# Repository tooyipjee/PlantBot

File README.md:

# Plant Bot: Automate Plant Care 🌱

## High-Level Summary

Plant Bot is a cutting-edge device designed to revolutionize plant care. Powered by USB, it seamlessly integrates into your pot, transforming it into an active participant in plant care. With features like a moisture sensor, integrated pump driver, and multi-color LED control, it's the ultimate companion for every plant enthusiast.

Available on 

---

## Detailed Description

### What is it?

Plant Bot is not just a device; it's a solution to modern plant care challenges. Designed for both casual plant owners and enthusiasts, it offers:

- **Corrosion-Resistant Capacitive Moisture Sensor:** Say goodbye to guesswork. Know exactly when your plant needs water.
- **Integrated Pump Driver & LED Control:** Automated care with visual feedback. The LED's color spectrum ranges from red (indicating dry soil) to blue (indicating moist soil).
- **Connectivity:** With both WiFi and Bluetooth capabilities, stay connected with your plants from anywhere.
- **Battery-Powered Operation:** Designed as a low-power IoT device, ensuring longevity and reliability.

Leveraging open-source projects, Plant Bot supports programming via Micropython and Arduino. For advanced users, the ESP-IDF tool offers maximum customization.

---

## Use Cases

### Fully Automated Plant Care

The sample code provided showcases Plant Bot's capabilities in measuring soil moisture and light levels, taking actions based on the data. The intuitive LED color spectrum offers a visual representation of soil conditions, while an additional LED signals pump activation for hydration. Built on the ESP32 platform, it boasts comprehensive connectivity, transmitting data to platforms like Thingspeak.

### Connected Plant Node

Harness the power of Plant Bot's low-power design to connect your plants to the internet wirelessly. Demos are available that allow Plant Bot to send Telegram notifications or relay measurements to IoT platforms. With efficient power consumption, a single coin cell battery can last up to a week with daily updates.

---

## How to Run the Demo Script

1. **Setup:** Ensure you have the Arduino IDE installed on your computer.
2. **Connect:** Plug in your ESP32-C3 device to your computer via USB.
3. **Integrated JTAG:** Ensure the JTAG is setup. In Tools, "USB CDC On Boot" is Enabled and JTAG Adapter is USB JTAG Adapter.
5. **Load Script:** Open one of the demo script provided in the Arduino IDE.
6. **Select Board:** From the 'Tools' menu, select 'Board' and choose 'ESP32-C3'.
7. **Select Port:** Select the port for the Plant-Bot device, if nothing pops up, unplug the device, hold the settings button and plug it back into the computer while still holding the button. It should appear now.
8. **Upload:** Click on the 'Upload' button to program the ESP32-C3.
9. **Monitor:** Open the Serial Monitor to view outputs and ensure the script runs successfully.

For any issues or further instructions, please refer to the documentation or raise an issue in the repo.

---

**Acknowledgments:** A special thank you to JLCPCB for their unwavering support throughout this project. Their expertise in rapid prototyping without compromising on quality has been invaluable.

## License

MIT License

Copyright (c) 2023 elektroThing

Permission is hereby granted, free of charge, to any person obtaining a copy
of this software and associated documentation files (the "Software"), to deal
in the Software without restriction, including without limitation the rights
to use, copy, modify, merge, publish, distribute, sublicense, and/or sell
copies of the Software, and to permit persons to whom the Software is
furnished to do so, subject to the following conditions:

The above copyright notice and this permission notice shall be included in all
copies or substantial portions of the Software.

THE SOFTWARE IS PROVIDED "AS IS", WITHOUT WARRANTY OF ANY KIND, EXPRESS OR
IMPLIED, INCLUDING BUT NOT LIMITED TO THE WARRANTIES OF MERCHANTABILITY,
FITNESS FOR A PARTICULAR PURPOSE AND NONINFRINGEMENT. IN NO EVENT SHALL THE
AUTHORS OR COPYRIGHT HOLDERS BE LIABLE FOR ANY CLAIM, DAMAGES OR OTHER
LIABILITY, WHETHER IN AN ACTION OF CONTRACT, TORT OR OTHERWISE, ARISING FROM,
OUT OF OR IN CONNECTION WITH THE SOFTWARE OR THE USE OR OTHER DEALINGS IN THE
SOFTWARE.

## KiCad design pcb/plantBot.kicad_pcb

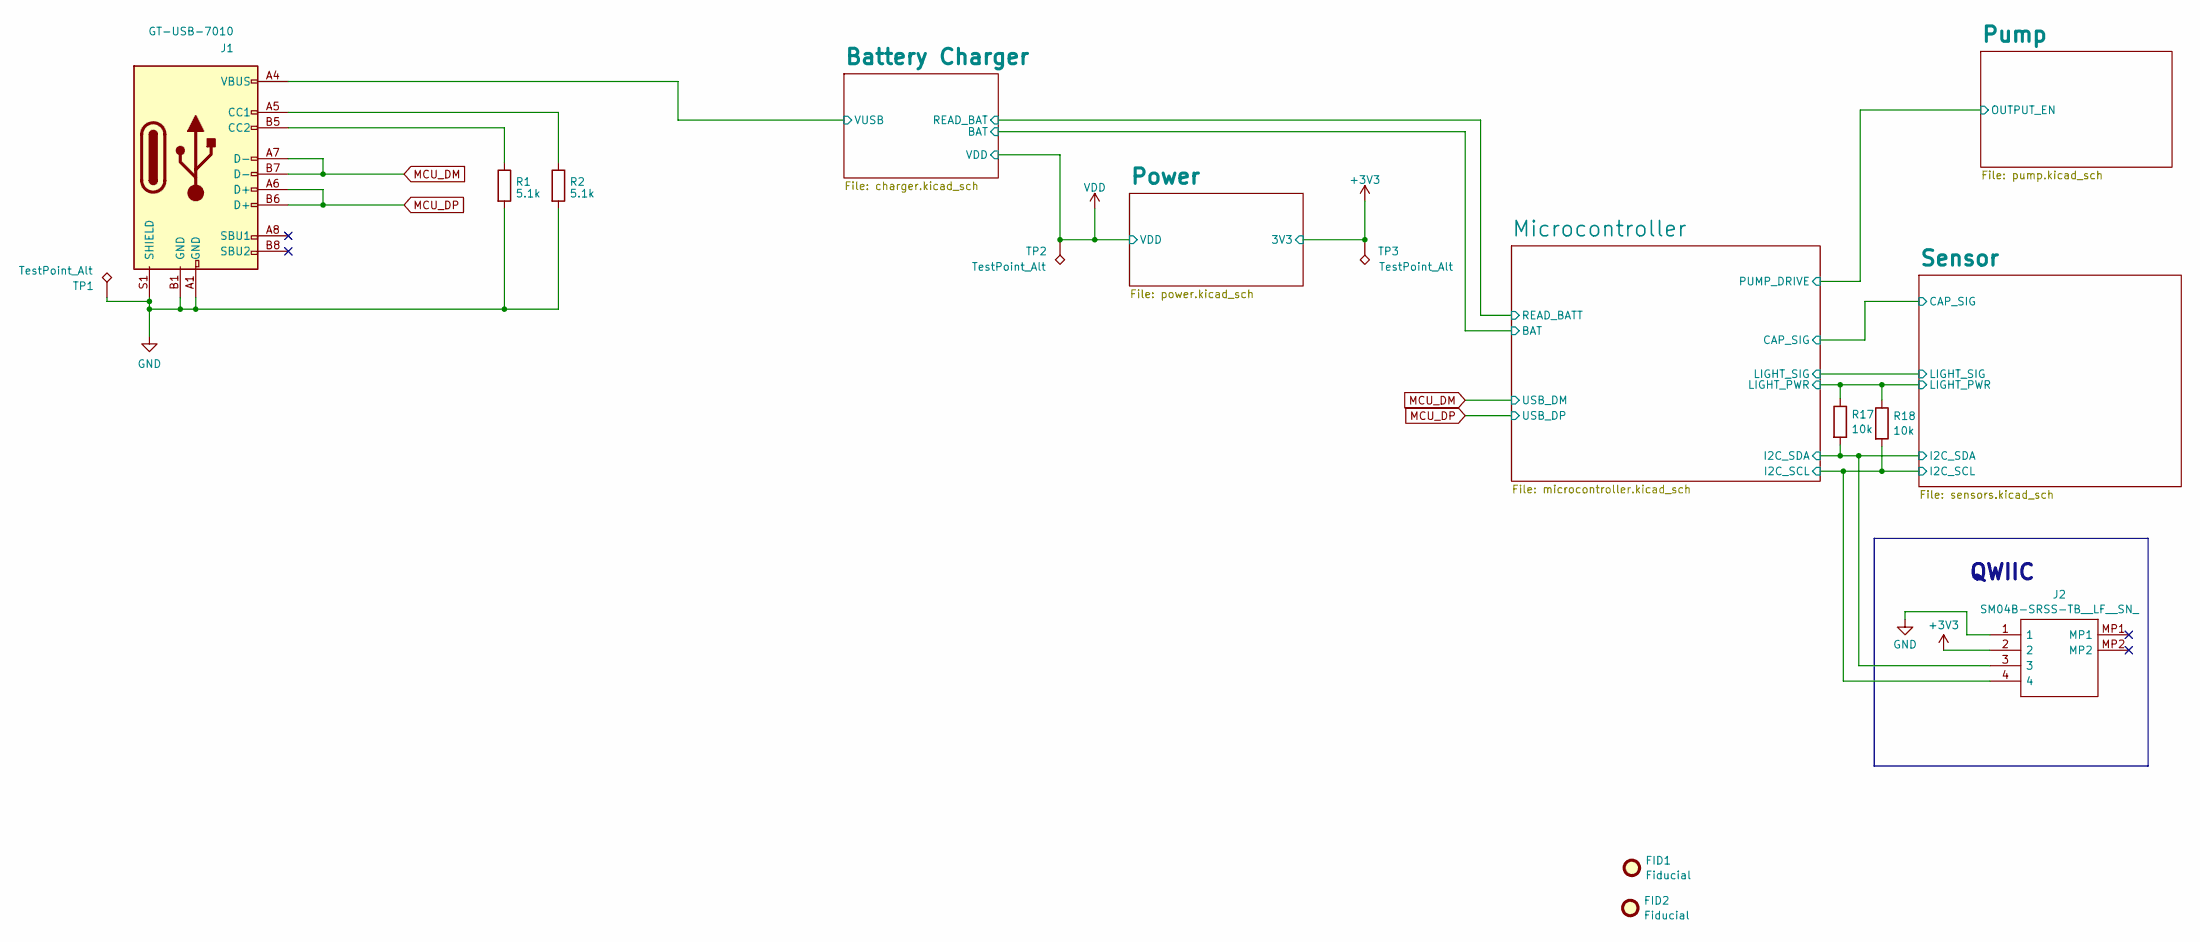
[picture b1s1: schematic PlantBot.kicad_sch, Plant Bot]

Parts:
FID1: Fiducial; Product Stamp
FID2: Fiducial; jlcpcb_logo_2mm
J1: GT-USB-7010; GT-USB-7010A; LCSC C963370
J2: SM04B-SRSS-TB__LF__SN_; SM04BSRSSTBLFSN; Manufacturer_Part_Number SM04B-SRSS-TB (LF)(SN); LCSC C160404
R1, R2: 5.1k; R_0402_1005Metric; LCSC C2906948
R17, R18: 10k; R_0402_1005Metric; LCSC C25744
TP1, TP2, TP3: TestPoint_Alt; TestPoint_Pad_1.0x1.0mm

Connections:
+3V3: J2.2, TP3.1; also elsewhere on the board
/Battery Charger/VUSB: J1.A4 (VBUS), J1.A9 (VBUS), J1.B4 (VBUS), J1.B9 (VBUS); also elsewhere on the board
/Microcontroller/I2C_SCL: J2.4, R18.2; also elsewhere on the board
/Microcontroller/I2C_SDA: J2.3, R17.2; also elsewhere on the board
GND: J1.A1 (GND), J1.B1 (GND), J1.S1 (SHIELD), J2.1, R1.2, R2.2, TP1.1; also elsewhere on the board
I2C_PWR: R17.1, R18.1; also elsewhere on the board
MCU_DM: J1.A7 (D-), J1.B7 (D-); also elsewhere on the board
MCU_DP: J1.A6 (D+), J1.B6 (D+); also elsewhere on the board
unnamed: J1.A5 (CC1), R2.1
unnamed: J1.B5 (CC2), R1.1
VDD: TP2.1; also elsewhere on the board

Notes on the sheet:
QWIIC

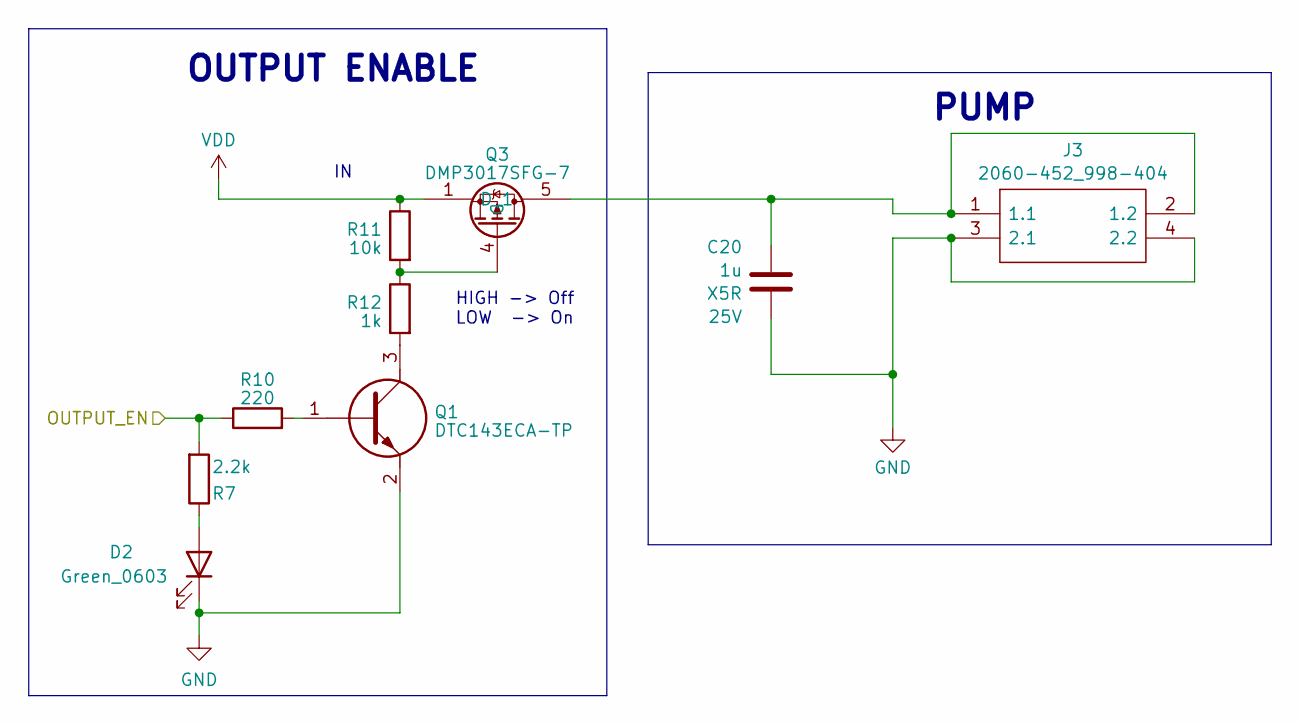
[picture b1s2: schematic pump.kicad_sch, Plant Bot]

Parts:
C20: 1u; C_0402_1005Metric; Voltage 25V; LCSC C52923
D2: Green_0603; LED_0603_1608Metric; LCSC C72043
J3: 2060-452_998-404; 2060452998404; Manufacturer_Part_Number 2060-452/998-404; LCSC C2765055
Q1: DTC143ECA-TP; SOT95P237X125-3N; Manufacturer_Part_Number DTC143ECA-TP; Mouser Part Number 833-DTC143ECA-TP
Q3: DMP3017SFG-7; DMP3007SFG7; Manufacturer_Part_Number DMP3017SFG-7; Mouser Part Number 621-DMP3017SFG-7
R7: 2.2k; R_0402_1005Metric; LCSC C25879
R10: 220; R_0402_1005Metric; LCSC C25091
R11: 10k; R_0402_1005Metric; LCSC C25744
R12: 1k; R_0402_1005Metric; LCSC C11702

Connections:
/Microcontroller/PUMP_DRIVE: R7.2, R10.1; also elsewhere on the board
GND: C20.2, D2.1 (K), J3.3 (2.1), J3.4 (2.2), Q1.2; also elsewhere on the board
unnamed: D2.2 (A), R7.1
unnamed: C20.1, J3.1 (1.1), J3.2 (1.2), Q3.5 (D_1), Q3.6, Q3.7, Q3.8, Q3.9
unnamed: Q1.1, R10.2
unnamed: Q1.3, R12.2
unnamed: Q3.4 (G), R11.2, R12.1
VDD: Q3.1, Q3.2, Q3.3, R11.1; also elsewhere on the board

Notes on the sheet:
OUTPUT ENABLE
PUMP
HIGH -> Off LOW -> On

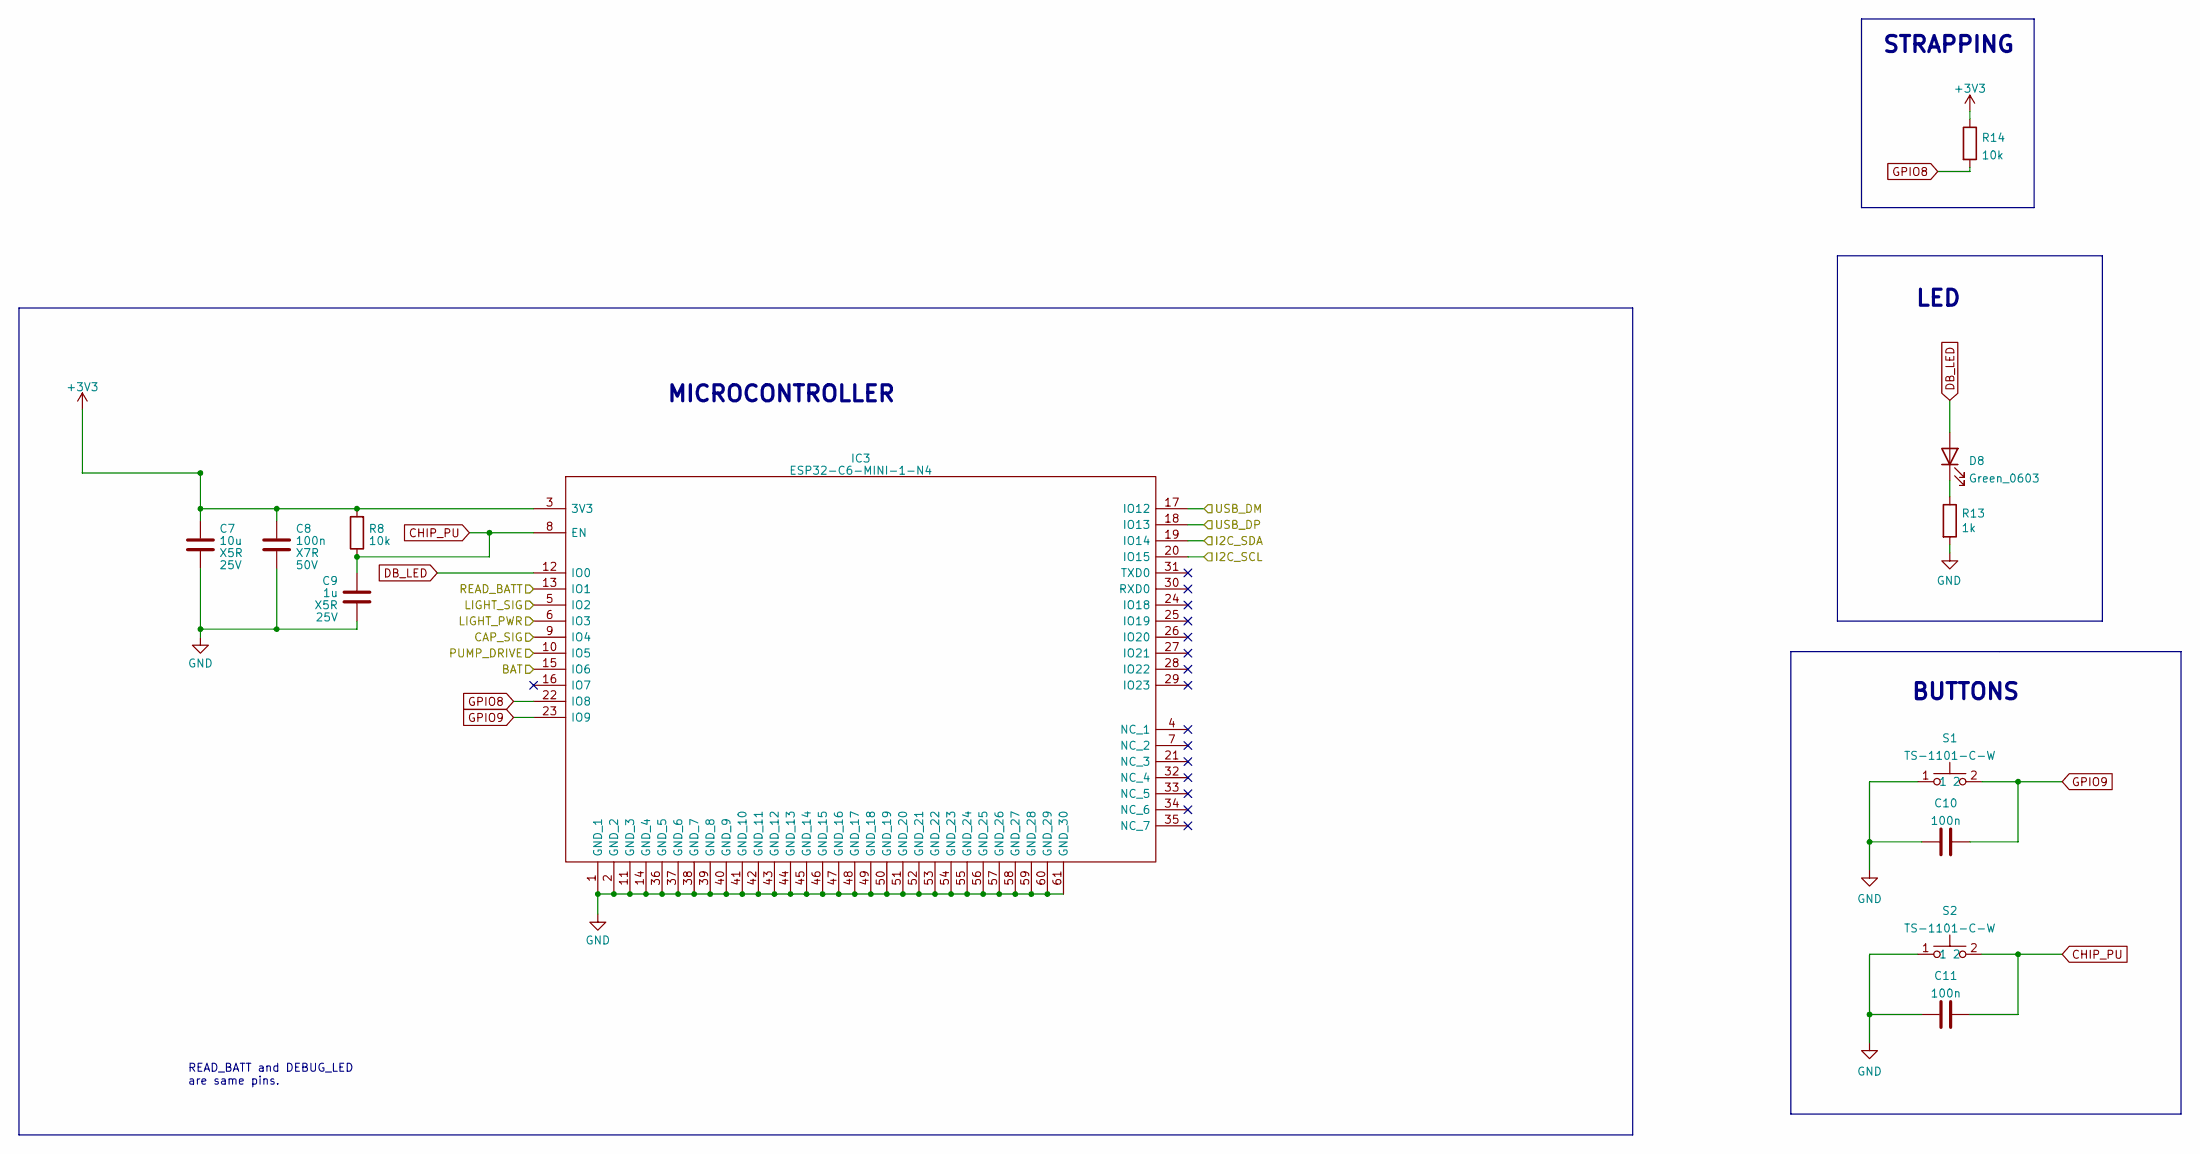
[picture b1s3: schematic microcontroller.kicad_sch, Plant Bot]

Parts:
C7: 10u; C_0805_2012Metric; Voltage 25V; LCSC C15850
C8: 100n; C_0402_1005Metric; Voltage 50V; LCSC C307331
C9: 1u; C_0402_1005Metric; Voltage 25V; LCSC C52923
C10, C11: 100n; C_0402_1005Metric; LCSC C307331
D8: Green_0603; LED_0603_1608Metric; LCSC C72043
IC3: ESP32-C6-MINI-1-N4; ESP32C6MINI1N4; Manufacturer_Part_Number ESP32-C6-MINI-1-N4; Mouser Part Number 356-ESP32C6MINI-1-N4
R8, R14: 10k; R_0402_1005Metric; LCSC C25744
R13: 1k; R_0402_1005Metric; LCSC C11702
S1, S2: TS-1101-C-W; TS1101CW; Manufacturer_Part_Number TS-1101-C-W; LCSC C318938

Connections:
+3V3: C7.1, C8.1, IC3.3 (3V3), R8.2, R14.1; also elsewhere on the board
/Battery Charger/BAT: IC3.15 (IO6); also elsewhere on the board
/Battery Charger/READ_BAT: IC3.13 (IO1); also elsewhere on the board
/Microcontroller/CAP_SIG: IC3.9 (IO4); also elsewhere on the board
/Microcontroller/I2C_SCL: IC3.20 (IO15); also elsewhere on the board
/Microcontroller/I2C_SDA: IC3.19 (IO14); also elsewhere on the board
/Microcontroller/LIGHT_SIG: IC3.5 (IO2); also elsewhere on the board
/Microcontroller/PUMP_DRIVE: IC3.10 (IO5); also elsewhere on the board
CHIP_PU: C9.2, C11.2, IC3.8 (EN), R8.1, S2.2
DB_LED: D8.2 (A), IC3.12 (IO0)
GND: C7.2, C8.2, C9.1, C10.1, C11.1, IC3.1 (GND_1), IC3.2 (GND_2), IC3.11 (GND_3), IC3.14 (GND_4), IC3.36 (GND_5), IC3.37 (GND_6), IC3.38 (GND_7), IC3.39 (GND_8), IC3.40 (GND_9), IC3.41 (GND_10), IC3.42 (GND_11), IC3.43 (GND_12), IC3.44 (GND_13), IC3.45 (GND_14), IC3.46 (GND_15), IC3.47 (GND_16), IC3.48 (GND_17), IC3.49 (GND_18), IC3.50 (GND_19), IC3.51 (GND_20), IC3.52 (GND_21), IC3.53 (GND_22), IC3.54 (GND_23), IC3.55 (GND_24), IC3.56 (GND_25), IC3.57 (GND_26), IC3.58 (GND_27), IC3.59 (GND_28), IC3.60 (GND_29), IC3.61 (GND_30), R13.2, S1.1, S2.1; also elsewhere on the board
GPIO8: IC3.22 (IO8), R14.2
GPIO9: C10.2, IC3.23 (IO9), S1.2
I2C_PWR: IC3.6 (IO3); also elsewhere on the board
MCU_DM: IC3.17 (IO12); also elsewhere on the board
MCU_DP: IC3.18 (IO13); also elsewhere on the board
unnamed: D8.1 (K), R13.1

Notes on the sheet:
STRAPPING
READ_BATT and DEBUG_LED are same pins.
LED
MICROCONTROLLER
BUTTONS

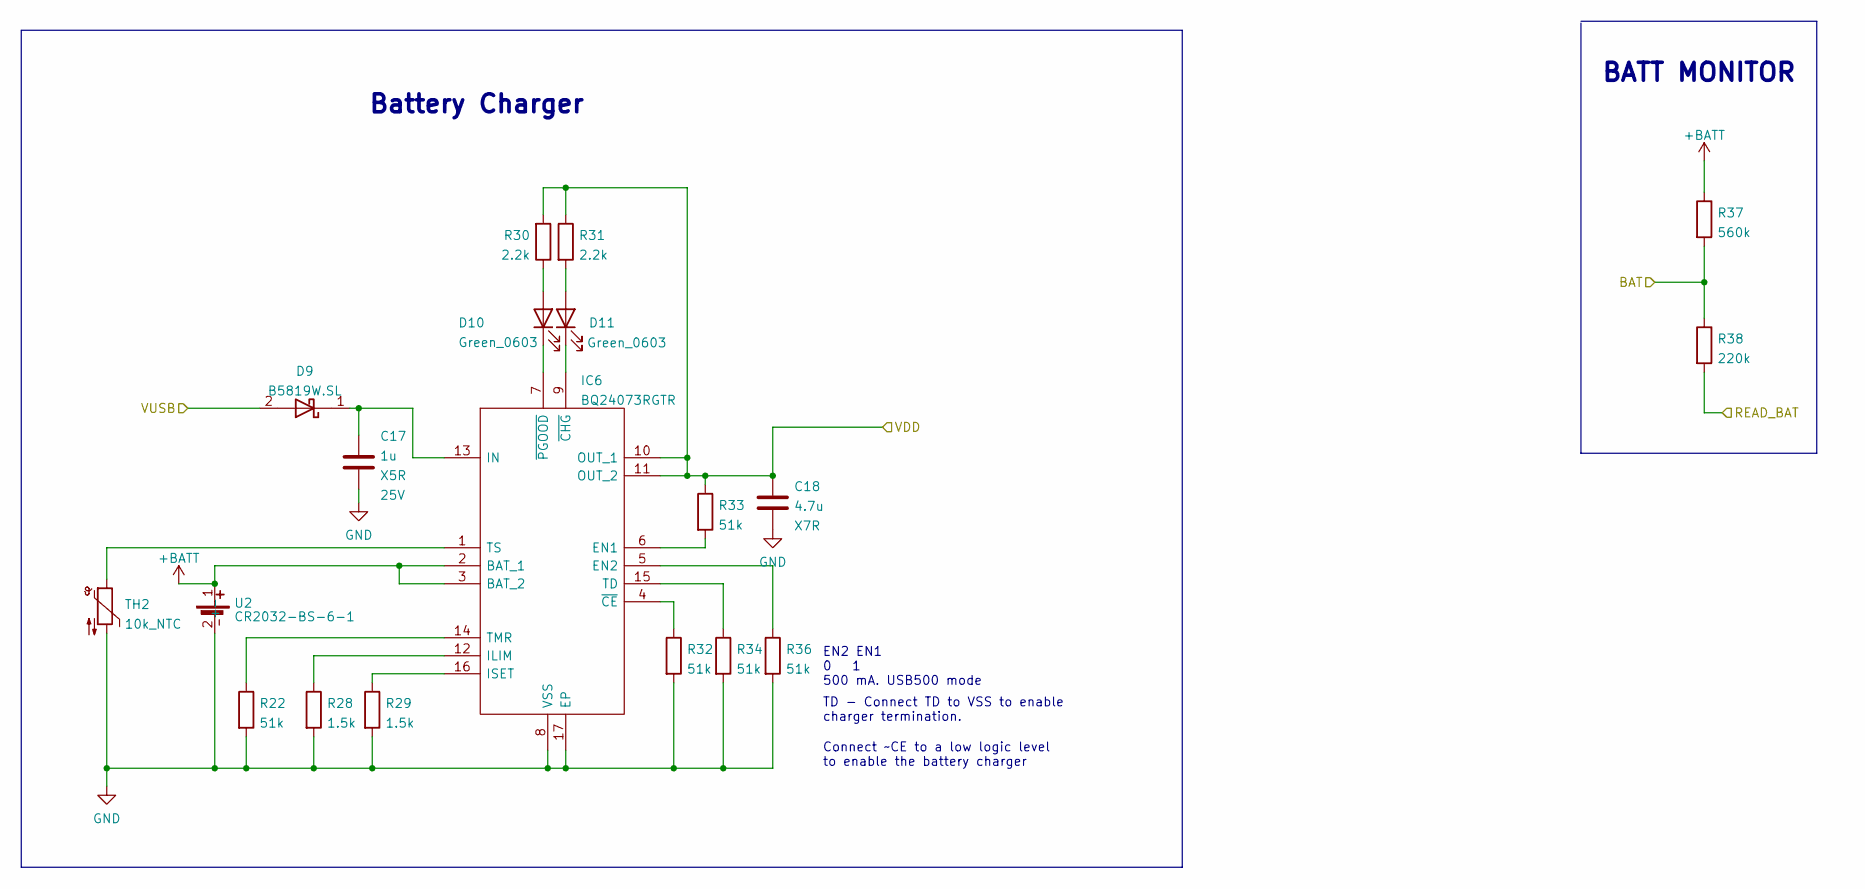
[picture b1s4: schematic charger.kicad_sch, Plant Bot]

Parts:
C17: 1u; C_0402_1005Metric; Voltage 25V; LCSC C52923
C18: 4.7u; C_1206_3216Metric; Rating 50V; LCSC C29823
D9: B5819W.SL; B5819WSL; Manufacturer_Part_Number B5819W.SL; LCSC C8598
D10, D11: Green_0603; LED_0603_1608Metric; LCSC C72043
IC6: BQ24073RGTR; QFN50P300X300X100-17N-D; Manufacturer_Part_Number BQ24073RGTR; Mouser Part Number 595-BQ24073RGTR
R22, R32, R33, R34, R36: 51k; R_0402_1005Metric; LCSC C25794
R28, R29: 1.5k; R_0402_1005Metric; LCSC C25867
R30, R31: 2.2k; R_0402_1005Metric; LCSC C25879
R37: 560k; R_0603_1608Metric; LCSC C23203
R38: 220k; R_0402_1005Metric; LCSC C25767
TH2: 10k_NTC; R_0402_1005Metric; MPN NCU15XH103F6SRC; LCSC C333993
U2: CR2032-BS-6-1; CR2032BS61; Manufacturer_Part_Number CR2032-BS-6-1; LCSC C70377

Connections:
+BATT: IC6.2 (BAT_1), IC6.3 (BAT_2), R37.1, U2.1 (+)
/Battery Charger/BAT: R37.2, R38.1; also elsewhere on the board
/Battery Charger/READ_BAT: R38.2; also elsewhere on the board
/Battery Charger/VUSB: D9.2; also elsewhere on the board
GND: C17.2, C18.2, IC6.8 (VSS), IC6.17 (EP), R22.2, R28.2, R29.2, R32.2, R34.2, R36.2, TH2.2, U2.2 (-); also elsewhere on the board
unnamed: D10.2 (A), R30.1
unnamed: D10.1 (K), IC6.7 (~PGOOD)
unnamed: D11.2 (A), R31.2
unnamed: D11.1 (K), IC6.9 (~CHG)
unnamed: IC6.6 (EN1), R33.2
unnamed: IC6.5 (EN2), R36.1
unnamed: IC6.12 (ILIM), R28.1
unnamed: C17.1, D9.1, IC6.13 (IN)
unnamed: IC6.16 (ISET), R29.1
unnamed: IC6.15 (TD), R34.1
unnamed: IC6.14 (TMR), R22.1
unnamed: IC6.1 (TS), TH2.1
unnamed: IC6.4 (~CE), R32.1
VDD: C18.1, IC6.10 (OUT_1), IC6.11 (OUT_2), R30.2, R31.1, R33.1; also elsewhere on the board

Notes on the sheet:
Connect ~CE to a low logic level to enable the battery charger
TD - Connect TD to VSS to enable charger termination.
Battery Charger
BATT MONITOR
EN2 EN1 0 1 500 mA. USB500 mode

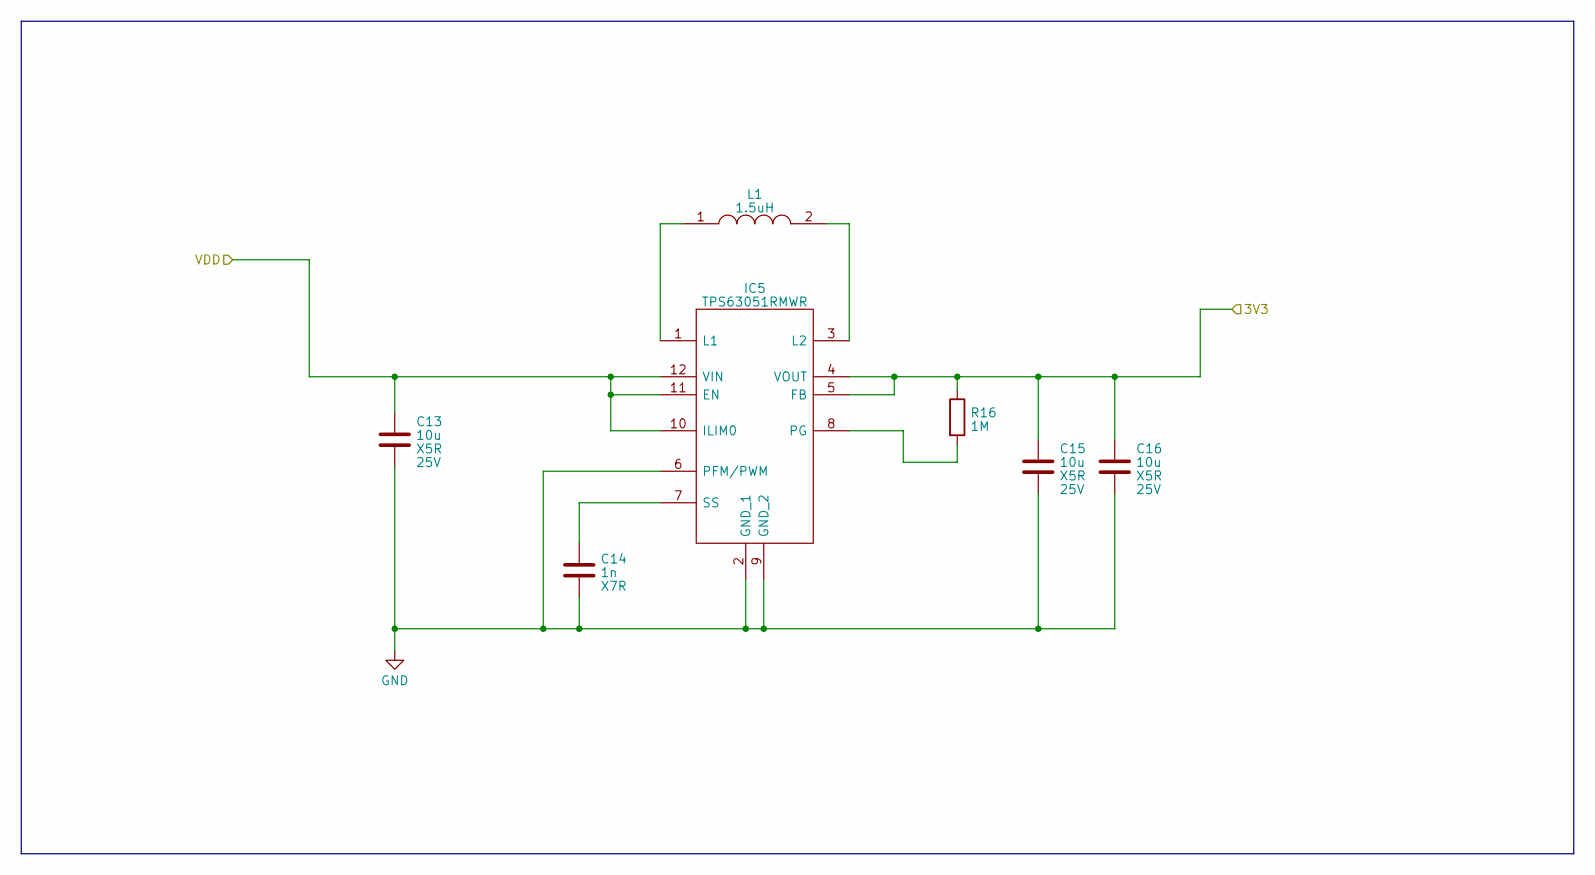
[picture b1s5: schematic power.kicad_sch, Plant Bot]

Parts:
C13, C15, C16: 10u; C_0805_2012Metric; Voltage 25V; LCSC C15850
C14: 1n; C_0402_1005Metric; LCSC C1523
IC5: TPS63051RMWR; QFN50P250X250X100-12N-D; Manufacturer_Part_Number TPS63051RMWR; Mouser Part Number 595-TPS63051RMWR
L1: 1.5uH; L_0805_2012Metric; LCSC C2042639
R16: 1M; R_0402_1005Metric; LCSC C26083

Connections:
+3V3: C15.1, C16.1, IC5.4 (VOUT), IC5.5 (FB), R16.1; also elsewhere on the board
GND: C13.2, C14.2, C15.2, C16.2, IC5.2 (GND_1), IC5.6 (PFM/PWM), IC5.9 (GND_2); also elsewhere on the board
unnamed: IC5.1 (L1), L1.1
unnamed: IC5.3 (L2), L1.2
unnamed: IC5.8 (PG), R16.2
unnamed: C14.1, IC5.7 (SS)
VDD: C13.1, IC5.10 (ILIM0), IC5.11 (EN), IC5.12 (VIN); also elsewhere on the board

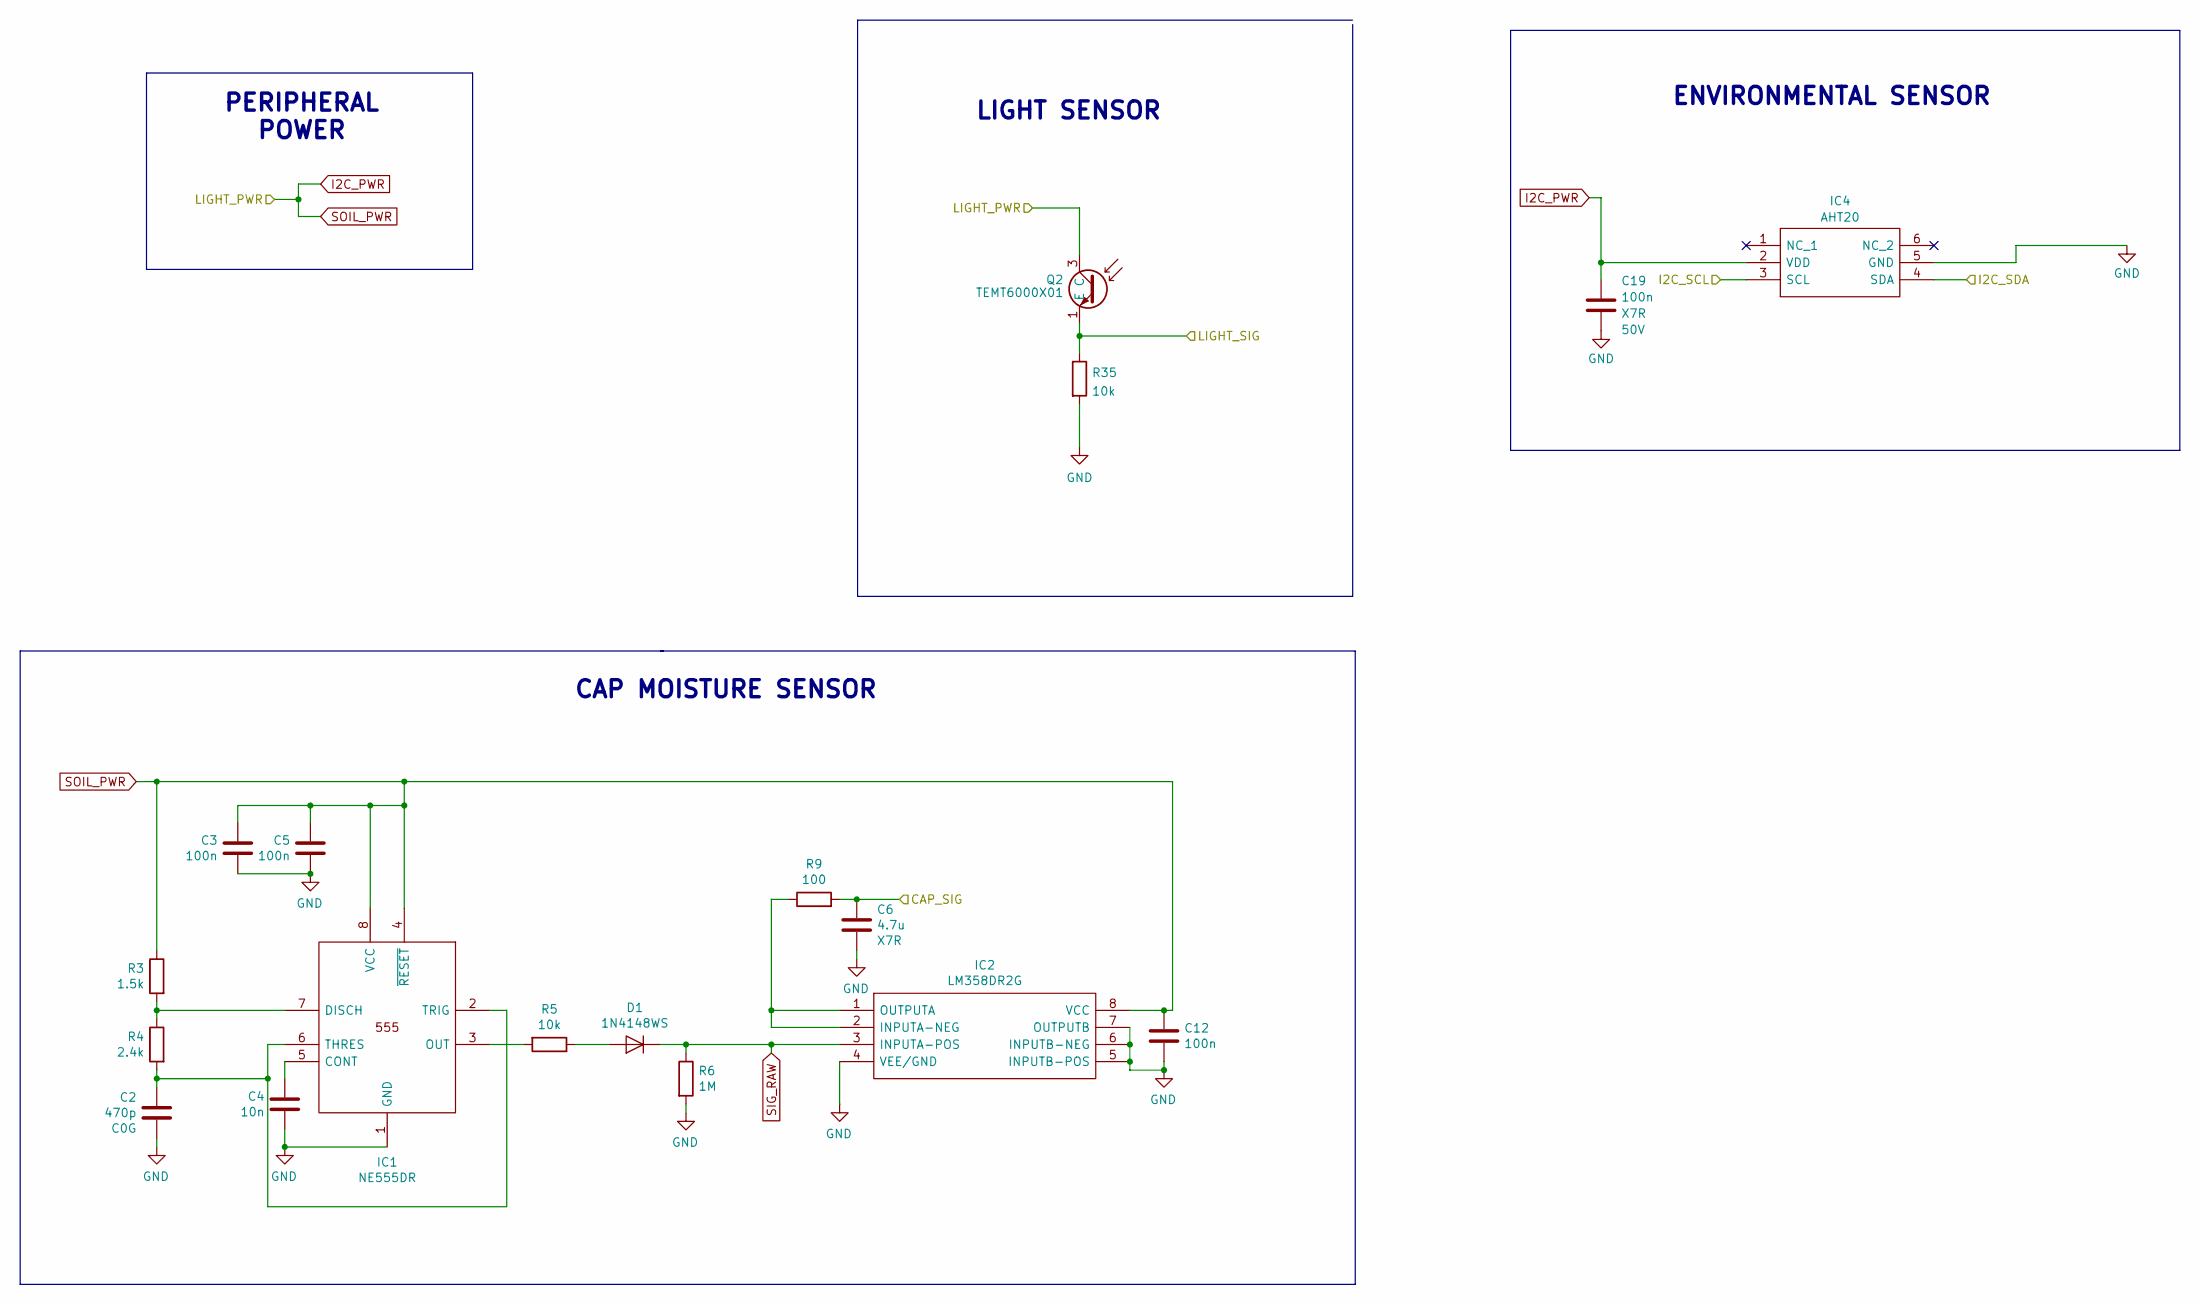
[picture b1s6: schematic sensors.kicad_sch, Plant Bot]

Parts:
C2: 470p; C_0603_1608Metric; Rating 25V; LCSC C1620
C3, C5, C12: 100n; C_0402_1005Metric; LCSC C307331
C4: 10n; C_0402_1005Metric; LCSC C15195
C6: 4.7u; C_1206_3216Metric; Rating 50V; LCSC C29823
C19: 100n; C_0402_1005Metric; Voltage 50V; LCSC C307331
D1: 1N4148WS; D_SOD-323F; LCSC C2128
IC1: NE555DR; SOIC127P600X175-8N; Manufacturer_Part_Number NE555DR; Mouser Part Number 595-NE555DR
IC2: LM358DR2G; SOIC127P600X175-8N; Mouser Part Number 863-LM358DR2G
IC4: AHT20; Manufacturer_Part_Number AHT20; LCSC C2757850
Q2: TEMT6000X01; Manufacturer_Part_Number TEMT6000X01; Mouser Part Number 78-TEMT6000
R3: 1.5k; R_0402_1005Metric; LCSC C25867
R4: 2.4k; R_0402_1005Metric; LCSC C25882
R5, R35: 10k; R_0402_1005Metric; LCSC C25744
R6: 1M; R_0402_1005Metric; LCSC C26083
R9: 100; R_0402_1005Metric; LCSC C25076

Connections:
/Microcontroller/CAP_SIG: C6.1, R9.2; also elsewhere on the board
/Microcontroller/I2C_SCL: IC4.3 (SCL); also elsewhere on the board
/Microcontroller/I2C_SDA: IC4.4 (SDA); also elsewhere on the board
/Microcontroller/LIGHT_SIG: Q2.1 (E), Q2.2 (E), R35.1; also elsewhere on the board
GND: C2.2, C3.2, C4.2, C5.2, C6.2, C12.2, C19.2, IC1.1 (GND), IC2.4 (VEE/GND), IC2.5 (INPUTB-POS), IC2.6 (INPUTB-NEG), IC2.7 (OUTPUTB), IC4.5 (GND), R6.2, R35.2; also elsewhere on the board
I2C_PWR: C3.1, C5.1, C12.1, C19.1, IC1.4 (~RESET), IC1.8 (VCC), IC2.8 (VCC), IC4.2 (VDD), Q2.3 (C), R3.1; also elsewhere on the board
unnamed: D1.2 (A), R5.1
unnamed: C4.1, IC1.5 (CONT)
unnamed: IC1.7 (DISCH), R3.2, R4.1
unnamed: IC1.3 (OUT), R5.2
unnamed: C2.1, IC1.2 (TRIG), IC1.6 (THRES), R4.2
unnamed: IC2.1 (OUTPUTA), IC2.2 (INPUTA-NEG), R9.1
SIG_RAW: D1.1 (K), IC2.3 (INPUTA-POS), R6.1

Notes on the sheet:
ENVIRONMENTAL SENSOR
CAP MOISTURE SENSOR
PERIPHERAL POWER
LIGHT SENSOR

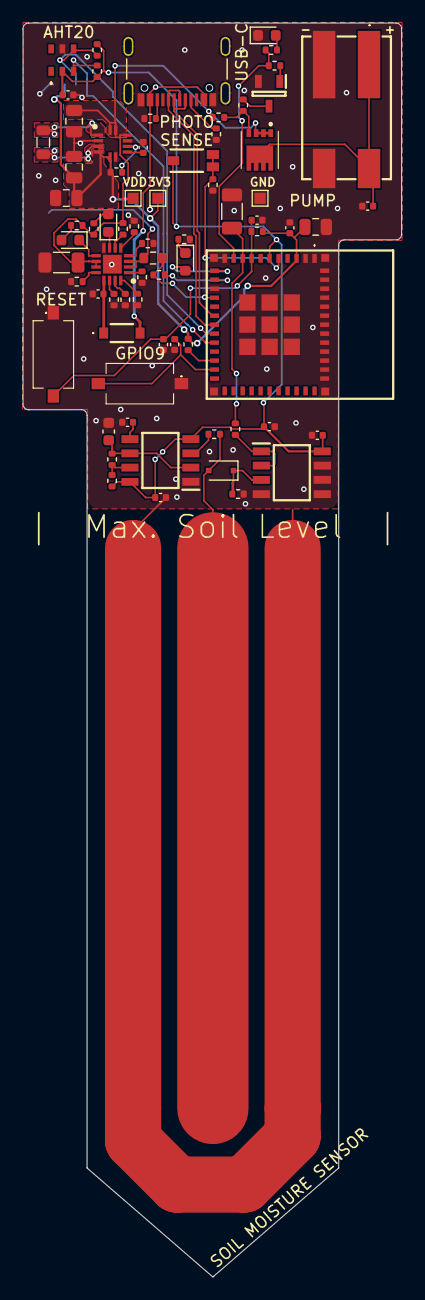
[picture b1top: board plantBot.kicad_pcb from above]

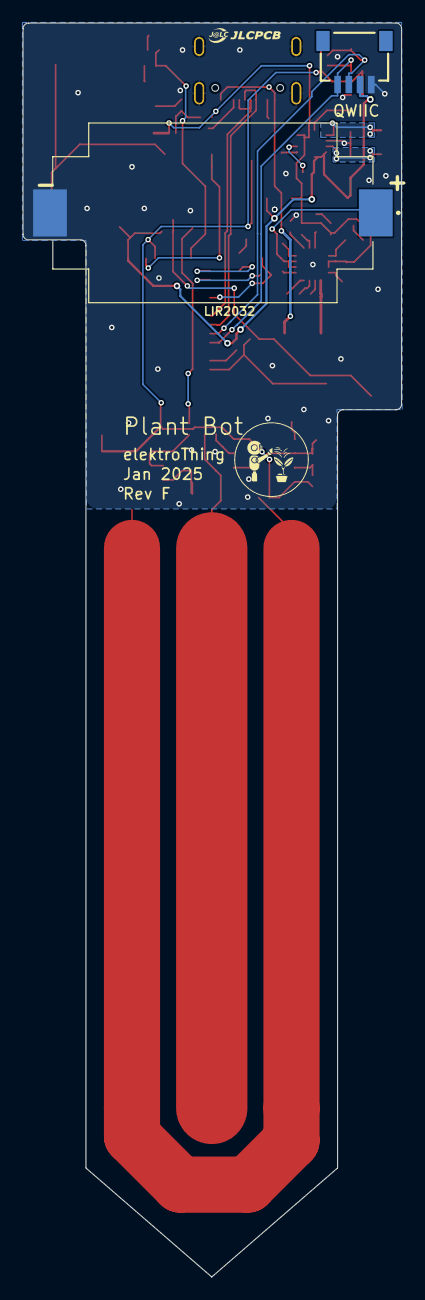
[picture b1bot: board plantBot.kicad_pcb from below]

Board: 2 copper layers, 33.7 x 111.6 mm, 77 parts (5 on the bottom side), 51 nets.

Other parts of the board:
F*: LOGO; logo_10mm

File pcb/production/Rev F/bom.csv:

Designator,Footprint,Quantity,Value,LCSC Part #
"C10, C11, C12, C19, C3, C5, C8",0402,7,100n,C307331
"C13, C15, C16, C7",0805,4,10u,C15850
C14,0402,1,1n,C1523
"C17, C20, C9",0402,3,1u,C52923
"C18, C6",1206,2,4.7u,C29823
C2,0603,1,470p,C1620 
C4,0402,1,10n,C15195
D1,D_SOD-323F,1,1N4148WS,C2128
"D10, D11, D2, D8",0603,4,Green_0603,C72043
D9,B5819WSL,1,B5819W.SL,C8598
IC1,SOIC127P600X175-8N,1,NE555DR,C7593
IC2,SOIC127P600X175-8N,1,LM358DR2G,C7950
IC3,ESP32C6MINI1N4,1,ESP32-C6-MINI-1-N4,C5736265
IC4,AHT20,1,AHT20,C2757850
IC5,QFN50P250X250X100-12N-D,1,TPS63051RMWR,C139412
IC6,QFN50P300X300X100-17N-D,1,BQ24073RGTR,C15220
J1,GT-USB-7010A,1,GT-USB-7010,C963370
J2,SM04BSRSSTBLFSN,1,SM04B-SRSS-TB__LF__SN_,C160404
J3,2060452998404,1,2060-452_998-404,C2765055
L1,0805,1,1.5uH,C2042639
Q1,SOT95P237X125-3N,1,DTC143ECA-TP,
Q2,TEMT6000X01,1,TEMT6000X01,C94098
Q3,DMP3007SFG7,1,DMP3017SFG-7,DMP3017SFG
"R1, R2",0402,2,5.1k,C2906948
R10,0402,1,220,C25091
"R11, R14, R17, R18, R35, R5, R8",0402,7,10k,C25744
"R12, R13",0402,2,1k,C11702
"R16, R6",0402,2,1M,C26083
"R22, R32, R33, R34, R36",0402,5,51k,C25794
"R28, R29, R3",0402,3,1.5k,C25867
"R30, R31, R7",0402,3,2.2k,C25879
R37,0603,1,560k,C23203
R38,0402,1,220k,C25767
R4,0402,1,2.4k,C25882
R9,0402,1,100,C25076
"S1, S2",TS1101CW,2,TS-1101-C-W,C318938
TH2,0402,1,10k_NTC,C333993
"TP1, TP2, TP3",TestPoint_Pad_1.0x1.0mm,3,TestPoint_Alt,
U2,CR2032BS61,1,CR2032-BS-6-1,C70377

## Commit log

2023-06-19 created step file
2023-08-13 Added demo scripts
2023-08-13 Updated with latest production files and code
2023-08-13 update photos
2023-11-25 Updated demo
2025-01-11 Restored pcb design
2025-01-11 Completed initial schematic
2025-01-18 updated design
2025-01-18 created fab files
2025-01-22 updated prod files with fiducials
2025-02-14 Created firmware files
